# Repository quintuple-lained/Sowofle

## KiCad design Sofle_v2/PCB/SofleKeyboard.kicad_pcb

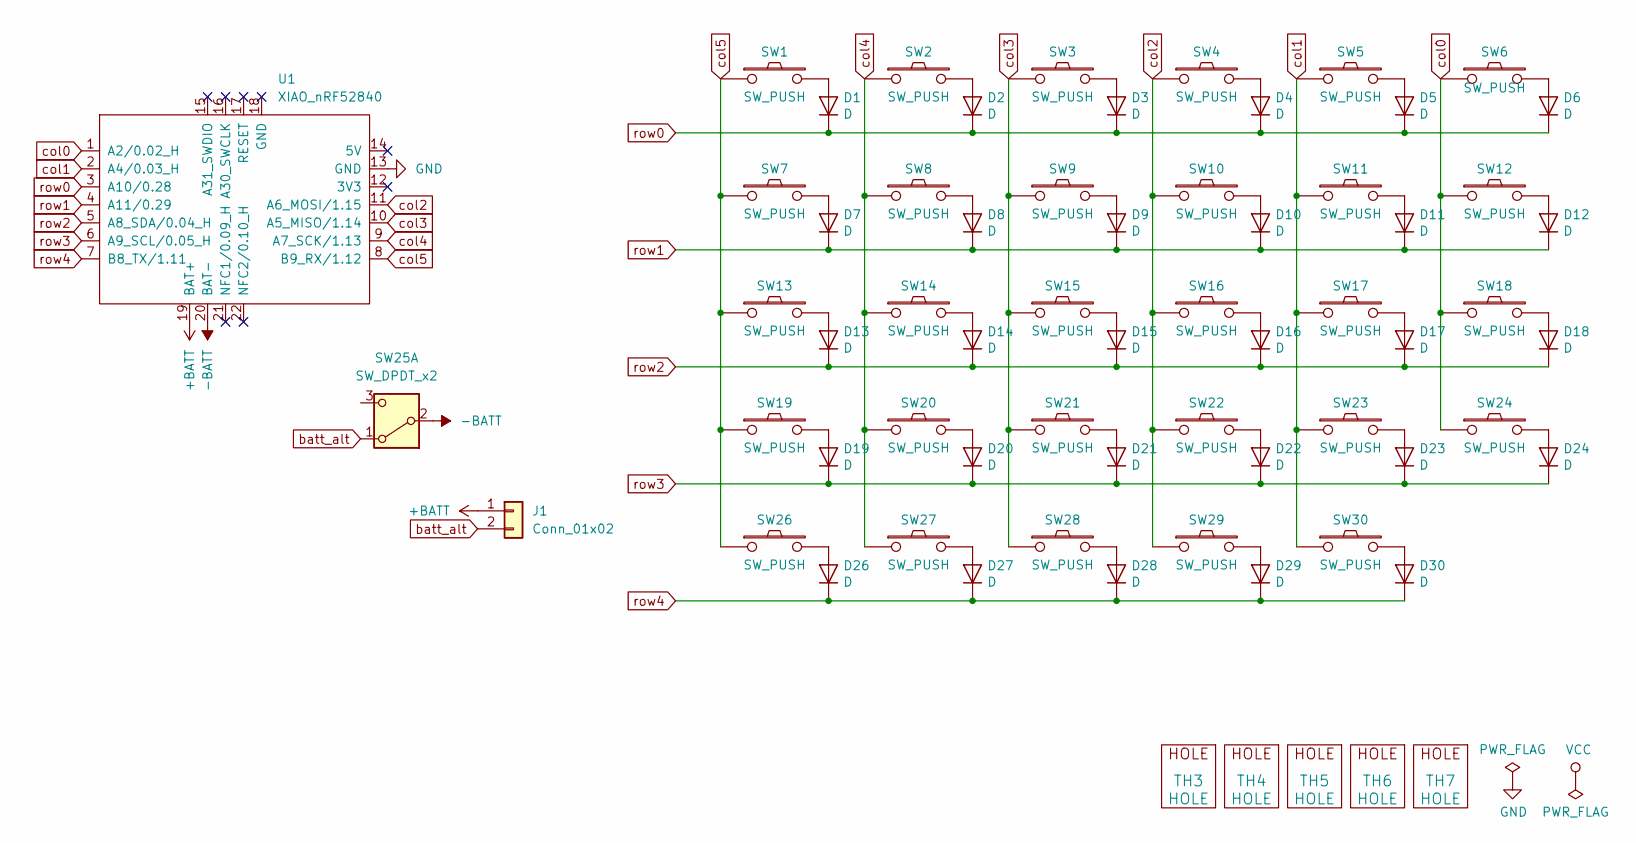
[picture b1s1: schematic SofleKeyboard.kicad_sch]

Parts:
D1, D2, D3, D4, D5, D6, D7, D8, D9, D10, D11, D12, D13, D14, D15, D16, D17, D18, D19, D20, D21, D22, D23, D24, D26, D27, D28, D29, D30: D; D_SOD-123_flip
J1: Conn_01x02; Battery
SW1, SW2, SW3, SW4, SW5, SW6, SW7, SW8, SW9, SW10, SW11, SW12, SW13, SW14, SW15, SW16, SW17, SW18, SW19, SW20, SW21, SW22, SW23, SW24, SW27, SW28, SW29, SW30: SW_PUSH; CherryMX_Hotswap
SW25: SW_DPDT_x2; MSK-12C02_DUAL
SW26: SW_PUSH; CherryMX_Hotswap_1.5
TH3, TH4, TH5, TH6, TH7: HOLE; HOLE_M2_TH
U1: XIAO_nRF52840; XIAO_nRF52840_DUAL

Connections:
+BATT: J1.1, U1.19 (BAT+)
-BATT: SW25.2 (B), U1.20 (BAT-)
GND: U1.13 (GND)
unnamed: D1.2 (A), SW1.2
unnamed: D2.2 (A), SW2.2
unnamed: D3.2 (A), SW3.2
unnamed: D4.2 (A), SW4.2
unnamed: D5.2 (A), SW5.2
unnamed: D6.2 (A), SW6.2
unnamed: D7.2 (A), SW7.2
unnamed: D8.2 (A), SW8.2
unnamed: D9.2 (A), SW9.2
unnamed: D10.2 (A), SW10.2
unnamed: D11.2 (A), SW11.2
unnamed: D12.2 (A), SW12.2
unnamed: D13.2 (A), SW13.2
unnamed: D14.2 (A), SW14.2
unnamed: D15.2 (A), SW15.2
unnamed: D16.2 (A), SW16.2
unnamed: D17.2 (A), SW17.2
unnamed: D18.2 (A), SW18.2
unnamed: D19.2 (A), SW19.2
unnamed: D20.2 (A), SW20.2
unnamed: D21.2 (A), SW21.2
unnamed: D22.2 (A), SW22.2
unnamed: D23.2 (A), SW23.2
unnamed: D24.2 (A), SW24.2
unnamed: D26.2 (A), SW26.2
unnamed: D27.2 (A), SW27.2
unnamed: D28.2 (A), SW28.2
unnamed: D29.2 (A), SW29.2
unnamed: D30.2 (A), SW30.2
batt_alt: J1.2, SW25.1 (A)
col0: SW6.1, SW12.1, SW18.1, SW24.1, U1.1 (A2/0.02_H)
col1: SW5.1, SW11.1, SW17.1, SW23.1, SW30.1, U1.2 (A4/0.03_H)
col2: SW4.1, SW10.1, SW16.1, SW22.1, SW29.1, U1.11 (A6_MOSI/1.15)
col3: SW3.1, SW9.1, SW15.1, SW21.1, SW28.1, U1.10 (A5_MISO/1.14)
col4: SW2.1, SW8.1, SW14.1, SW20.1, SW27.1, U1.9 (A7_SCK/1.13)
col5: SW1.1, SW7.1, SW13.1, SW19.1, SW26.1, U1.8 (B9_RX/1.12)
row0: D1.1 (K), D2.1 (K), D3.1 (K), D4.1 (K), D5.1 (K), D6.1 (K), U1.3 (A10/0.28)
row1: D7.1 (K), D8.1 (K), D9.1 (K), D10.1 (K), D11.1 (K), D12.1 (K), U1.4 (A11/0.29)
row2: D13.1 (K), D14.1 (K), D15.1 (K), D16.1 (K), D17.1 (K), D18.1 (K), U1.5 (A8_SDA/0.04_H)
row3: D19.1 (K), D20.1 (K), D21.1 (K), D22.1 (K), D23.1 (K), D24.1 (K), U1.6 (A9_SCL/0.05_H)
row4: D26.1 (K), D27.1 (K), D28.1 (K), D29.1 (K), D30.1 (K), U1.7 (B8_TX/1.11)

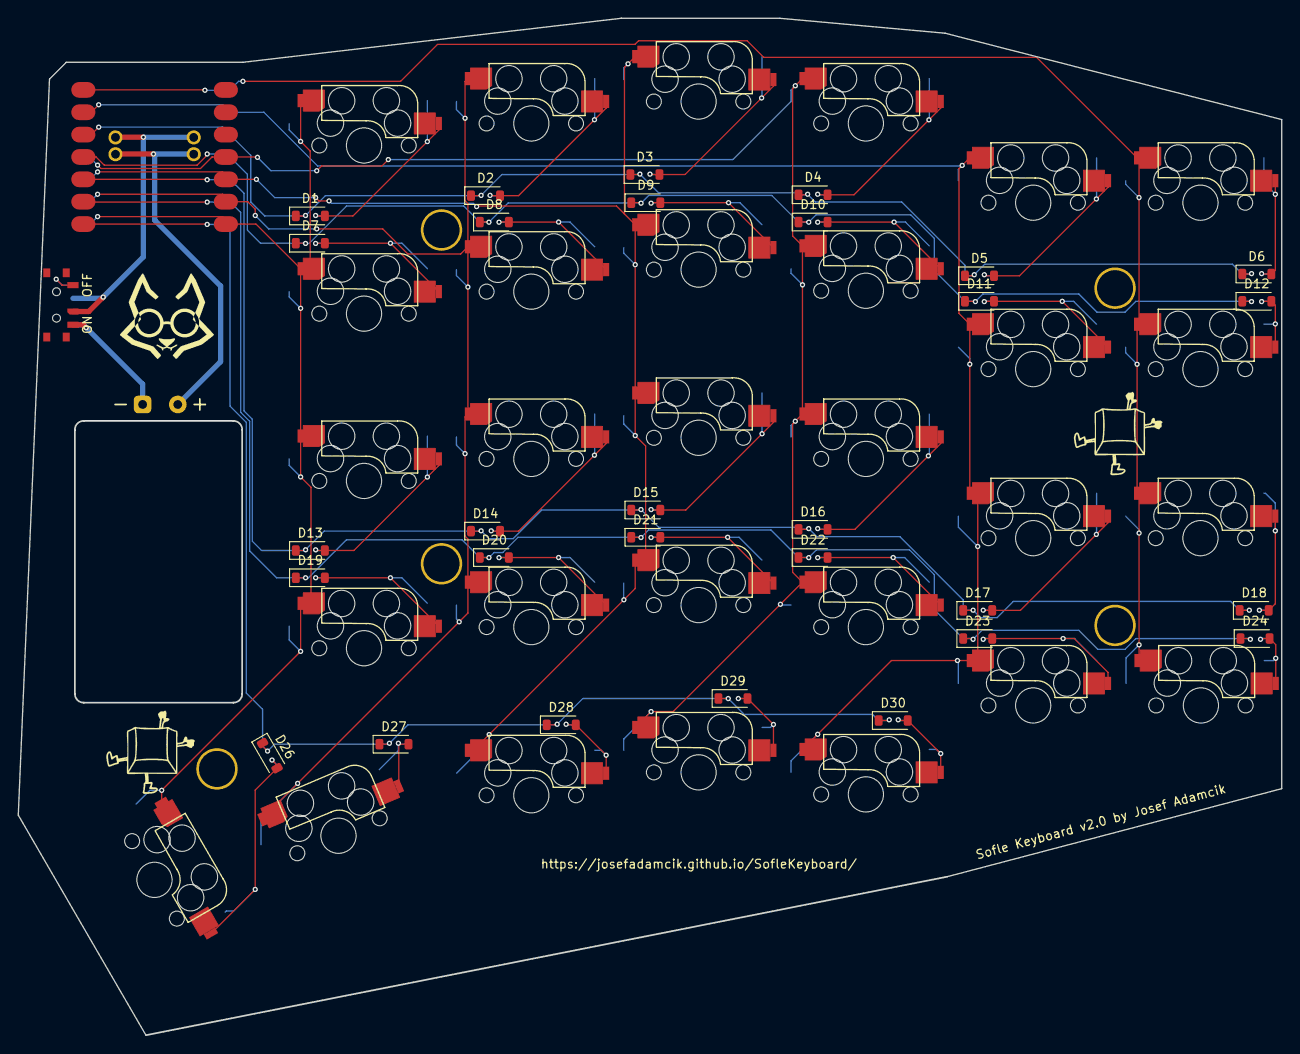
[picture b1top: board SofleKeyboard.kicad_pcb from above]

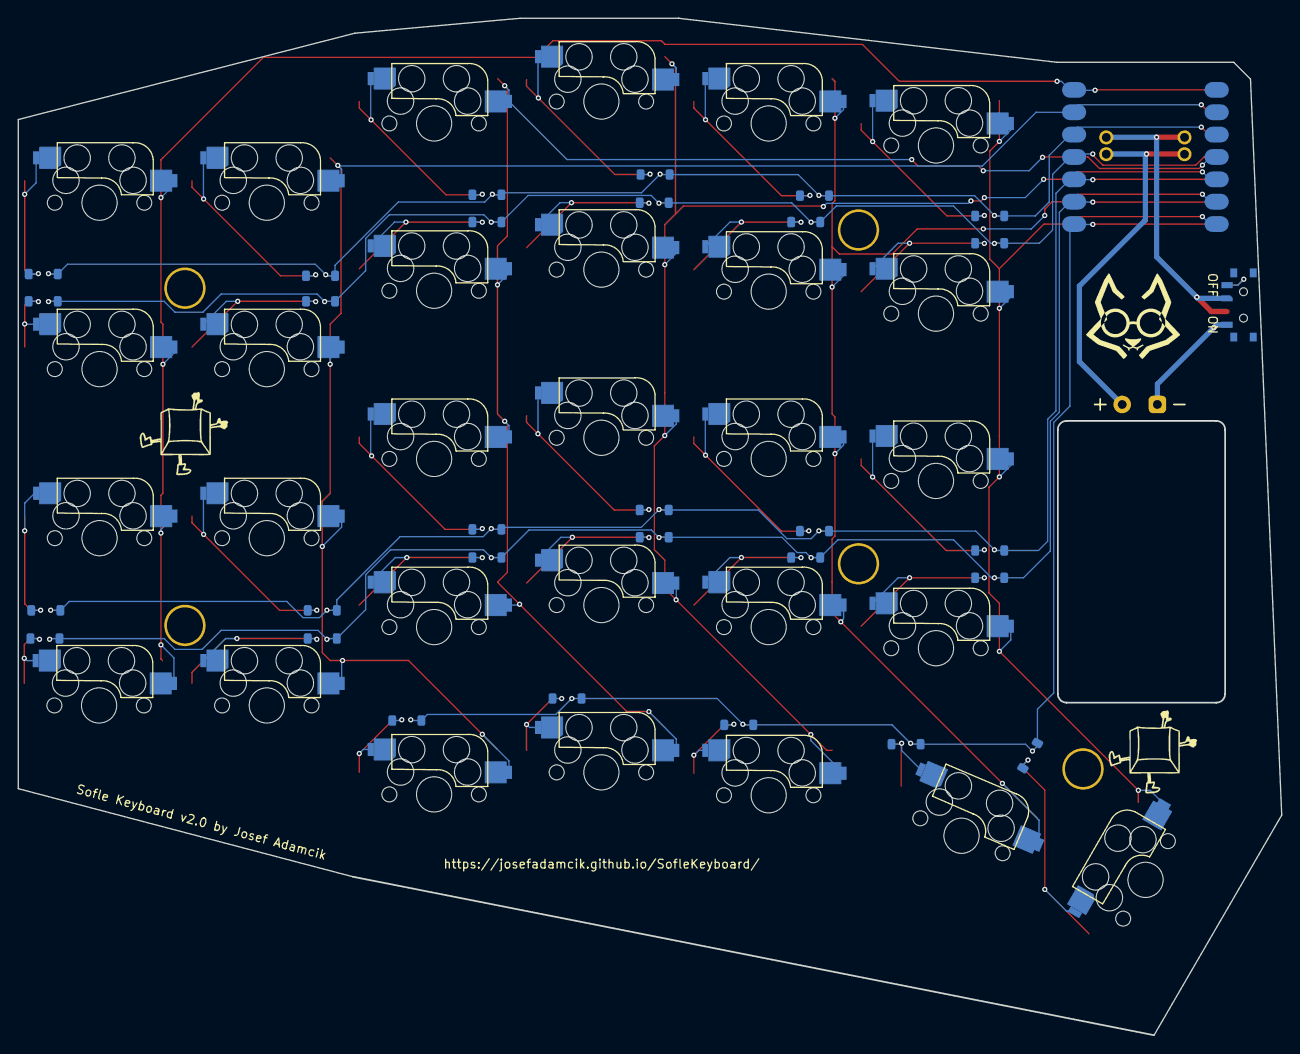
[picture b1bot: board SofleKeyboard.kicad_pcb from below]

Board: 2 copper layers, 143.5 x 115.5 mm, 70 parts (2 on the bottom side), 43 nets.

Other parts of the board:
Ref**: Val**; SofleLogoSmall
Ref**#2, Ref**#3, Ref**#4: Val**; SofleLogoSmall

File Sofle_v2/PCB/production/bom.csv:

Designator,Footprint,Quantity,Value,LCSC Part #
"D1, D10, D11, D12, D13, D14, D15, D16, D17, D18, D19, D2, D20, D21, D22, D23, D24, D26, D27, D28, D29, D3, D30, D4, D5, D6, D7, D8, D9",D_SOD-123_flip,29,D,
J1,Battery,1,Conn_01x02,
"SW1, SW10, SW11, SW12, SW13, SW14, SW15, SW16, SW17, SW18, SW19, SW2, SW20, SW21, SW22, SW23, SW24, SW27, SW28, SW29, SW3, SW30, SW4, SW5, SW6, SW7, SW8, SW9",CherryMX_Hotswap,28,SW_PUSH,
SW25,MSK-12C02_DUAL,1,SW_DPDT_x2,
SW26,CherryMX_Hotswap_1.5,1,SW_PUSH,
"TH3, TH4, TH5, TH6, TH7",HOLE_M2_TH,5,HOLE,
U1,XIAO_nRF52840_DUAL,1,XIAO_nRF52840,

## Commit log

2024-04-30 initial prototype
